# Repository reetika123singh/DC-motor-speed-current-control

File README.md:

# DRV8833 Dual H-Bridge Motor Driver — PCB and Cascade Speed & Current Control

A DC motor drive system built around the DRV8833 dual H-bridge driver, with a custom KiCad PCB and a Simulink/Simscape simulation of a cascade control architecture for precise speed regulation.

## Key Specifications

| Parameter | Value |
|---|---|
| Supply Voltage | 12 V |
| PWM Switching Frequency | 10 kHz |
| Speed Setpoint (simulated) | 1600 RPM |
| Current Limit (inner loop saturation) | 0 – 1.6 A |
| Control Architecture | Cascade: outer speed loop → inner current loop |

## Control Architecture

The system uses a **cascade (dual-loop) control structure**, which regulates motor speed while keeping motor current within a safe limit:

1. **Outer speed loop:**  PI controller (P = 0.002, I = 0.02) compares the RPM setpoint against measured speed and outputs a current command.
2. **Saturation stage:** The current command is clamped to 0–1.6 A, acting as a current limiter between the two loops.
3. **Inner current loop:** PI controller (P = 0.5, I = 5) compares the (limited) current command against sensed motor current and drives the H-Bridge PWM input.
4. **Plant:** An averaged H-Bridge model (12V, 10kHz) driving a Simscape DC Motor model (Ra = 2Ω, La = 1mH, Kv = 0.0072 V/rpm, J = 1e-5 kg·m²), with feedback from a Current Sensor (inner loop) and an Ideal Rotational Motion Sensor (outer loop, converted from rad/s to RPM).

## Repository Structure

- `Motor driver DRV8833.kicad_pro` (+ associated schematic/PCB files) — KiCad project for the DRV8833 driver board, including power rail decoupling and charge pump circuitry.
- `Motor_speed_control.slx` — Simulink/Simscape model implementing the cascade control loop described above.

## How to Run the Simulation

1. Open MATLAB and load `Motor_speed_control.slx` in Simulink.
2. Run the simulation to observe the motor speed settling toward the 1600 RPM setpoint and the current staying within the 0–1.6 A limit.
3. View the Scope block for speed and current response over time.

## PCB

## Results

1. **Settling time:** 0.12s
2. **Steady-state speed error:** +100 RPM
3. **Peak current during startup:** 1.4 A

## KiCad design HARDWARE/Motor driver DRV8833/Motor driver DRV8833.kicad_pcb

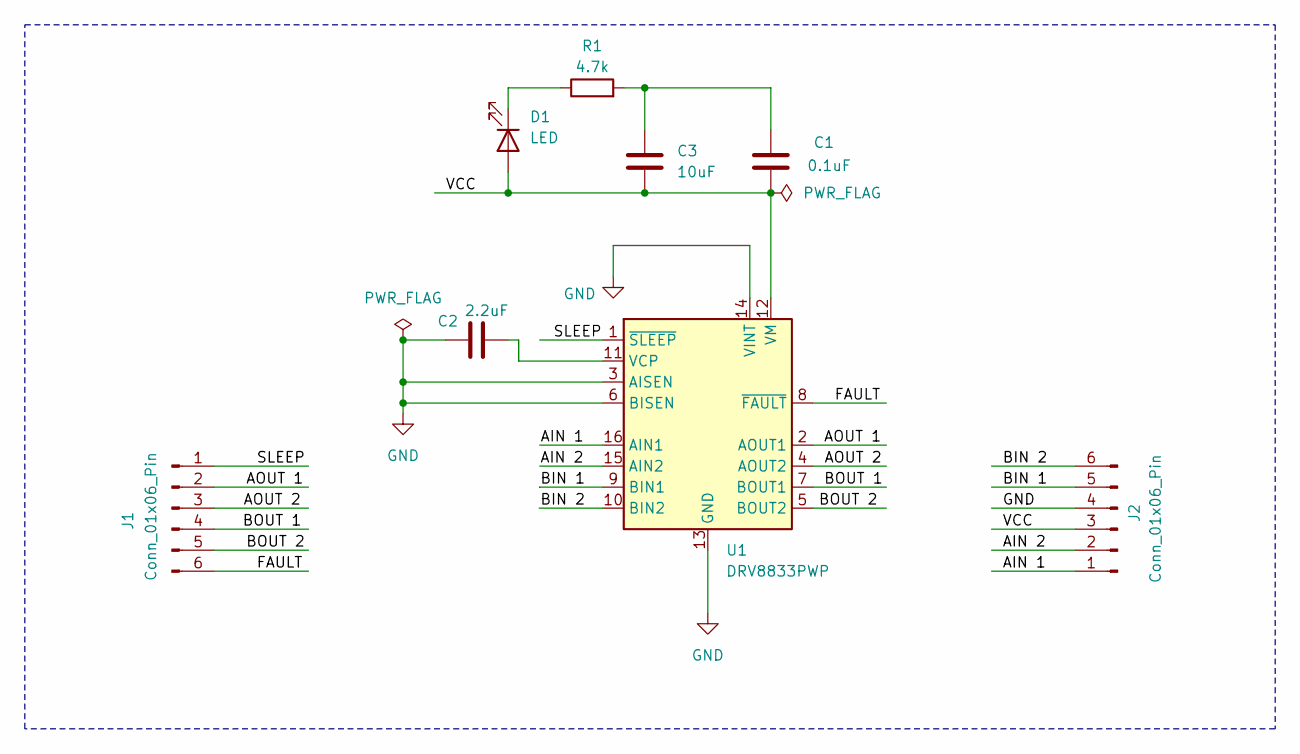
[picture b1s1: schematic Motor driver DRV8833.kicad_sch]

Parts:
C1: 0.1uF; C_0805_2012Metric
C2: 2.2uF; C_0805_2012Metric
C3: 10uF; CP_EIA-6032-20_AVX-F
D1: LED; LED_0805_2012Metric
J1, J2: Conn_01x06_Pin; PinHeader_1x06_P2.54mm_Vertical
R1: 4.7k; R_0805_2012Metric
U1: DRV8833PWP; HTSSOP-16-1EP_4.4x5mm_P0.65mm_EP3.4x5mm_Mask2.46x2.31mm_The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

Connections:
/AIN 1: J2.1, U1.16 (AIN1)
/AIN 2: J2.2, U1.15 (AIN2)
/AOUT 1: J1.2, U1.2 (AOUT1)
/AOUT 2: J1.3, U1.4 (AOUT2)
/BIN 1: J2.5, U1.9 (BIN1)
/BIN 2: J2.6, U1.10 (BIN2)
/BOUT 1: J1.4, U1.7 (BOUT1)
/BOUT 2: J1.5, U1.5 (BOUT2)
/FAULT: J1.6, U1.8 (~FAULT)
/SLEEP: J1.1, U1.1 (~SLEEP)
/VCC: C1.2, C3.2, D1.2 (A), J2.3, U1.12 (VM)
GND: C2.1, J2.4, U1.3 (AISEN), U1.6 (BISEN), U1.13 (GND), U1.14 (VINT), U1.17 (GND)
unnamed: C1.1, C3.1, R1.2
unnamed: D1.1 (K), R1.1
unnamed: C2.2, U1.11 (VCP)

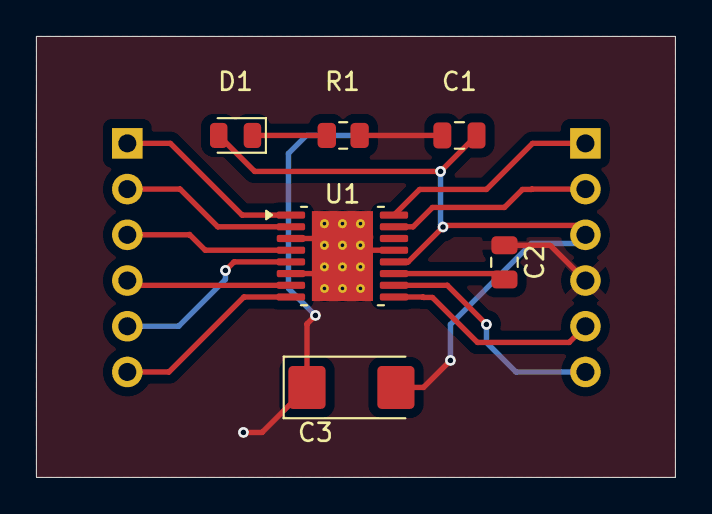
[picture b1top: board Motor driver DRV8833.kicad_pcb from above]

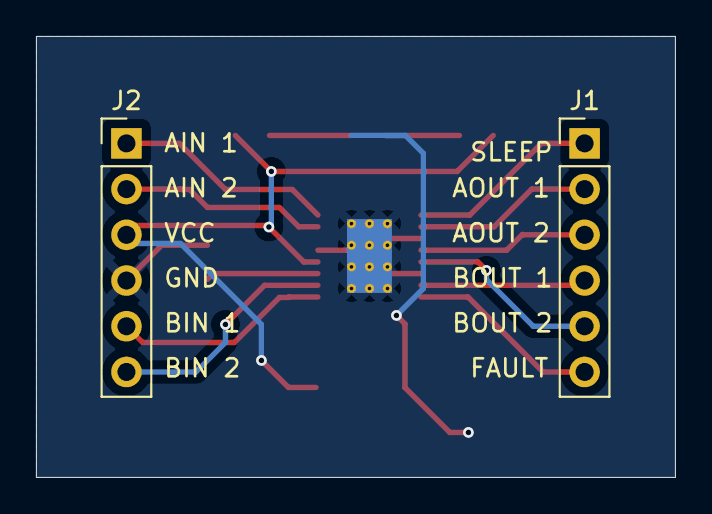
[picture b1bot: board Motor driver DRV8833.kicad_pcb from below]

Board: 2 copper layers, 35.5 x 24.5 mm, 8 parts (2 on the bottom side), 15 nets.
